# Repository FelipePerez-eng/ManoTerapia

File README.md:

# ManoTerapia

**METIE · Universidad de Ibagué · Ingeniería Electrónica**

**Equipo:** Felipe Perez · Brenda Guzman · David Solorzano

© 2026 Felipe Perez, Brenda Guzman y David Solorzano. Código y documentación originales bajo [licencia MIT](LICENSE). [Autoría, materiales de terceros y asistencia de IA](NOTICE.md).

Prototipo de mano robótica maestro–esclavo con ESP32, cinco potenciómetros y cinco servomotores MG90S. El dashboard permite usar control espejo, practicar gestos, ejecutar demostraciones, realizar rutinas y guardar resultados de pruebas en CSV.

## Qué archivo usar

| Necesitas… | Abre este archivo |
|---|---|
| Usar la interfaz | [dashboard/ManoTerapia.html](dashboard/ManoTerapia.html) |
| Cargar el programa al ESP32 | [firmware/ManoTerapia_ESP32/ManoTerapia_ESP32.ino](firmware/ManoTerapia_ESP32/ManoTerapia_ESP32.ino) |
| Abrir el proyecto electrónico | [hardware/kicad/Placa.kicad_pro](hardware/kicad/Placa.kicad_pro) |
| Consultar el esquema | [hardware/kicad/Placa.kicad_sch](hardware/kicad/Placa.kicad_sch) |
| Consultar la PCB | [hardware/kicad/Placa.kicad_pcb](hardware/kicad/Placa.kicad_pcb) |
| Ver pendientes y pruebas | [docs/estado.md](docs/estado.md) |
| Revisar los saltos esporádicos | [docs/estabilidad_electrica.md](docs/estabilidad_electrica.md) |

## Estructura

```text
ManoTerapia/
├── README.md
├── dashboard/
│   └── ManoTerapia.html
├── firmware/
│   └── ManoTerapia_ESP32/
│       └── ManoTerapia_ESP32.ino
├── hardware/
│   └── kicad/
│       ├── Placa.kicad_pro
│       ├── Placa.kicad_sch
│       ├── Placa.kicad_pcb
│       ├── fp-lib-table
│       ├── sym-lib-table
│       └── Library.pretty/
├── docs/
└── tests/
    └── verificar.cjs
```

Hay una sola copia vigente del dashboard y del firmware. Las versiones anteriores se consultan en el historial de Git, sin llenar la carpeta de archivos numerados. La organización no cambia el código operativo ni obliga a volver a cargarlo si ya estás usando la última versión.

## Puesta en marcha

1. Para programar la placa, abre el `.ino` en Arduino IDE desde su carpeta del mismo nombre. Selecciona tu placa ESP32 y puerto, e instala la biblioteca `ESP32Servo` si no está disponible.
2. Cierra el Monitor Serial antes de conectar el dashboard: utiliza una sola aplicación conectada al puerto a la vez.
3. Abre `dashboard/ManoTerapia.html` con Chrome o Edge de escritorio y pulsa **Conectar ESP32**. La comunicación usa **115200 baudios**. Si el navegador no admite Web Serial desde un archivo local, utiliza un contexto seguro compatible, como localhost.
4. Comprueba primero los porcentajes con los servos desactivados. Después activa el sistema y prueba movimientos lentos.
5. Para cambiar de sección durante una rutina o un gesto, primero pulsa **Finalizar**.

El HTML incorpora estilos, JavaScript y banner METIE; no necesita bibliotecas web externas. El historial de sesiones se guarda en el navegador. Exporta el CSV para conservar tus resultados. Cambiar de archivo, navegador u origen puede impedir acceder al historial anterior; exporta los datos antes de migrar.

## Funciones actuales

- **Control espejo:** la mano robótica sigue las lecturas de la mano maestra, con filtrado adaptativo, órdenes graduales e histéresis angular para reducir movimientos pequeños no deseados.
- **Activación:** antes de habilitar los servos, lee los cinco potenciómetros y calcula sus objetivos con la calibración vigente. Ya no impone siempre la posición abierta al activarlos. Esto no conoce la postura física previa ni garantiza eliminar el pico de corriente.
- **Rutinas:** activan los servos y esperan que el ESP32 confirme `SERVO ON` y modo `ROUTINE` antes de empezar. Si se apagan los servos o cambia el modo, la rutina queda en pausa y no valida ejercicios; **Reanudar rutina** vuelve a solicitar activación y conserva el paso. Muestran el objetivo y la lectura de cada dedo. La flexión intermedia admite de 30 % a 70 %; los demás pasos mantienen su margen de ±15 puntos. La posición se mantiene durante 1,2 segundos con recepción continua de datos.
- **Gestos:** mano abierta, puño, pulgar arriba, paz, señalamiento, pistolita y dedo medio. Una ventana flotante ofrece **Automático**, **Manual** y **Finalizar**, con opciones de minimizar y cerrar sin desplazar las tarjetas. Ocultar la ventana no finaliza una actividad.
- **Seguimiento:** sesiones locales, ciclos, muestras, actividades e informes CSV.

El corazón aparece como referencia deshabilitada: su reproducción requiere validar movimientos mecánicos que el control actual no implementa. Los sensores flex no se usan en el firmware vigente, aunque sus conectores aparecen en el diseño electrónico.

## Conexiones vigentes del firmware

| Dedo | GPIO del potenciómetro | GPIO del servo | RAW abierto | RAW cerrado |
|---|---:|---:|---:|---:|
| Pulgar | 33 | 23 | 4095 | 3800 |
| Índice | 32 | 22 | 4095 | 2700 |
| Medio | 35 | 21 | 4095 | 2500 |
| Anular | 34 | 19 | 4095 | 2800 |
| Meñique | 36 | 18 | 4095 | 3100 |

Estas correspondencias conservan las correcciones del usuario. No equivalen necesariamente al orden numérico de los conectores en la placa.

- Pulsador: **GPIO 4 a GND**, con `INPUT_PULLUP` y antirrebote de 60 ms.
- LED: **GPIO 13**, con resistencia de 330 Ω hacia el LED y GND.
- Potenciómetros: alimentación de **3,3 V**.
- Servos: **MG90S**, fuente externa de **5 V** indicada por el usuario. Capacidad en amperios pendiente de confirmar.
- Mantener una referencia GND común entre señales del ESP32 y alimentación de los servos.

La lectura disminuye al cerrar la mano. La calibración utiliza esos extremos sin invertir las señales de los servos. Un RAW que permanezca fijo en 4095 al mover el potenciómetro requiere revisar la lectura y sus conexiones; cambiar la calibración no repara una conexión intermitente.

## KiCad

Esquemático compartido por el equipo. Los conectores flex aparecen en el diseño, pero no se utilizan en el firmware vigente. Para consultar la edición actual, abre el archivo `.kicad_sch` del proyecto.

Los archivos proceden del proyecto `Placa` de METIE, creado con **KiCad 10**. Abre `Placa.kicad_pro` para trabajar con esquema y PCB. Se incluyen el símbolo ESP32 y sus huellas locales. En esta copia se normalizó la tabla de huellas para evitar entradas duplicadas y se añadió una tabla de símbolos con ruta relativa.

El esquema y la PCB no se rediseñaron durante la organización. Los modelos 3D externos no se incluyen; las huellas pueden conservar referencias a `KICAD_USER_3DMODEL_DIR`. No publicar archivos de fabricación como validados hasta revisar el diseño y su correspondencia con el montaje.

## Estado y límites

El usuario reportó mejoras tras resoldar conexiones y probar las variantes de calibración y filtrado. **Siguen pendientes los pequeños saltos esporádicos de los servos y la respuesta intermitente del pulsador.** No se consideran resueltos por la reorganización.

El dashboard mide señales de los potenciómetros de la mano maestra. No mide la posición física de la mano esclava. Una demostración terminada indica que acabó la secuencia de órdenes, no que la postura física se haya verificado. Las rutinas son demostraciones del prototipo académico, no un protocolo clínico validado.

## Cómo citar el proyecto

Si utilizas ManoTerapia como referencia en una presentación, trabajo académico o investigación, por favor incluye esta cita:

> Perez, F., Guzman, B., y Solorzano, D. (2026). *ManoTerapia* [Software de prototipo académico]. GitHub. https://github.com/FelipePerez-eng/ManoTerapia

El archivo [CITATION.cff](CITATION.cff) facilita la opción **Cite this repository** de GitHub. La cita académica se solicita como reconocimiento; la condición de MIT es conservar el aviso de copyright y la licencia en las copias o partes sustanciales correspondientes.

## Desarrollo con asistencia de IA

El proyecto contó con asistencia de **ChatGPT/Codex de OpenAI** para apoyar la programación, el diseño de la interfaz, la documentación, la revisión de código y las pruebas simuladas. La revisión e integración física corresponden al equipo. Esta asistencia no implica certificación técnica ni validación clínica.

Consulta [NOTICE.md](NOTICE.md) para el alcance de la licencia y los materiales de terceros, incluidos los recursos institucionales y las bibliotecas externas.

## Pruebas y versiones

Con Node.js, desde la carpeta principal:

```sh
node tests/verificar.cjs
```

Las pruebas son simuladas y no sustituyen compilar el firmware en Arduino IDE ni probar el prototipo. Consultar [docs/estado.md](docs/estado.md) para distinguir las verificaciones realizadas de las pendientes.

Repositorio: [FelipePerez-eng/ManoTerapia](https://github.com/FelipePerez-eng/ManoTerapia). Cada cambio debe quedar descrito en un commit; las versiones antiguas se recuperan desde ese historial. No subir datos personales de participantes, CSV de sesiones ni credenciales.

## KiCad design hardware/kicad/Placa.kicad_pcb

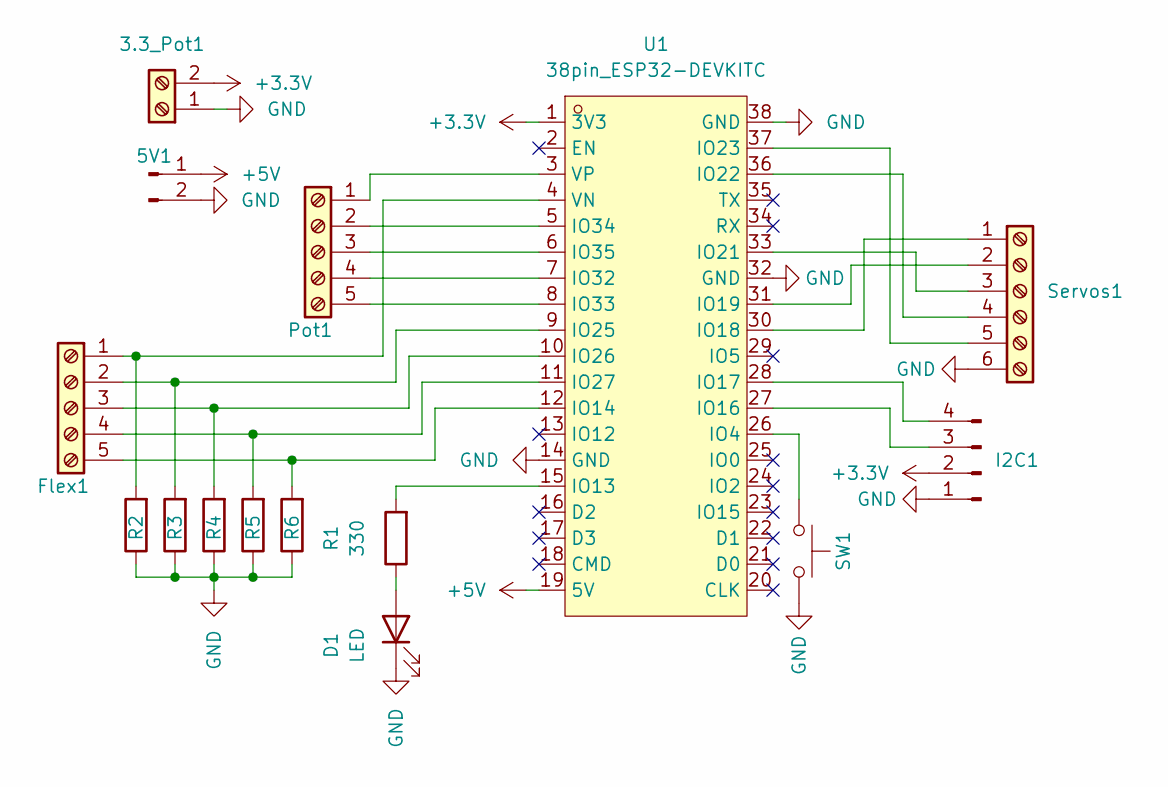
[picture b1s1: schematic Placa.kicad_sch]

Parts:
3.3_Pot1: Screw_Terminal_01x02; TerminalBlock_MaiXu_MX126-5.0-02P_1x02_P5.00mm
5V1: Conn_01x02_Pin; PinSocket_1x02_P2.54mm_Vertical
D1: LED; LED_D3.0mm
Flex1: Screw_Terminal_01x05; TerminalBlock_MaiXu_MX126-5.0-05P_1x05_P5.00mm
I2C1: Conn_01x04_Pin; PinHeader_1x04_P2.54mm_Vertical
Pot1: Screw_Terminal_01x05; TerminalBlock_MaiXu_MX126-5.0-05P_1x05_P5.00mm
R1, R2, R3, R4, R5, R6: 330; R_Axial_DIN0207_L6.3mm_D2.5mm_P10.16mm_Horizontal
SW1: SW_Push; SW_PUSH_6mm
Servos1: Screw_Terminal_01x06; TerminalBlock_MaiXu_MX126-5.0-06P_1x06_P5.00mm
U1: 38pin_ESP32-DEVKITC; Z_ESP32_DevKitC_38pin_socket; MPN ESP32-DevKitC; LCSC Part C571180

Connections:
+3.3V: 3.3_Pot1.2, I2C1.2, U1.1 (3V3)
+5V: 5V1.1, U1.19 (5V)
GND: 3.3_Pot1.1, 5V1.2, D1.1 (K), I2C1.1, R2.1, R3.1, R4.1, R5.1, R6.1, SW1.2, Servos1.6, U1.14 (GND), U1.32 (GND), U1.38 (GND)
unnamed: D1.2 (A), R1.1
unnamed: Flex1.1, R2.2, U1.4 (VN)
unnamed: Flex1.2, R3.2, U1.9 (IO25)
unnamed: Flex1.3, R4.2, U1.10 (IO26)
unnamed: Flex1.4, R5.2, U1.11 (IO27)
unnamed: Flex1.5, R6.2, U1.12 (IO14)
unnamed: I2C1.3, U1.27 (IO16)
unnamed: I2C1.4, U1.28 (IO17)
unnamed: Pot1.1, U1.3 (VP)
unnamed: Pot1.2, U1.5 (IO34)
unnamed: Pot1.3, U1.6 (IO35)
unnamed: Pot1.4, U1.7 (IO32)
unnamed: Pot1.5, U1.8 (IO33)
unnamed: Servos1.1, U1.30 (IO18)
unnamed: Servos1.2, U1.31 (IO19)
unnamed: Servos1.3, U1.33 (IO21)
unnamed: Servos1.4, U1.36 (IO22)
unnamed: Servos1.5, U1.37 (IO23)
unnamed: SW1.1, U1.26 (IO4)
unnamed: R1.2, U1.15 (IO13)

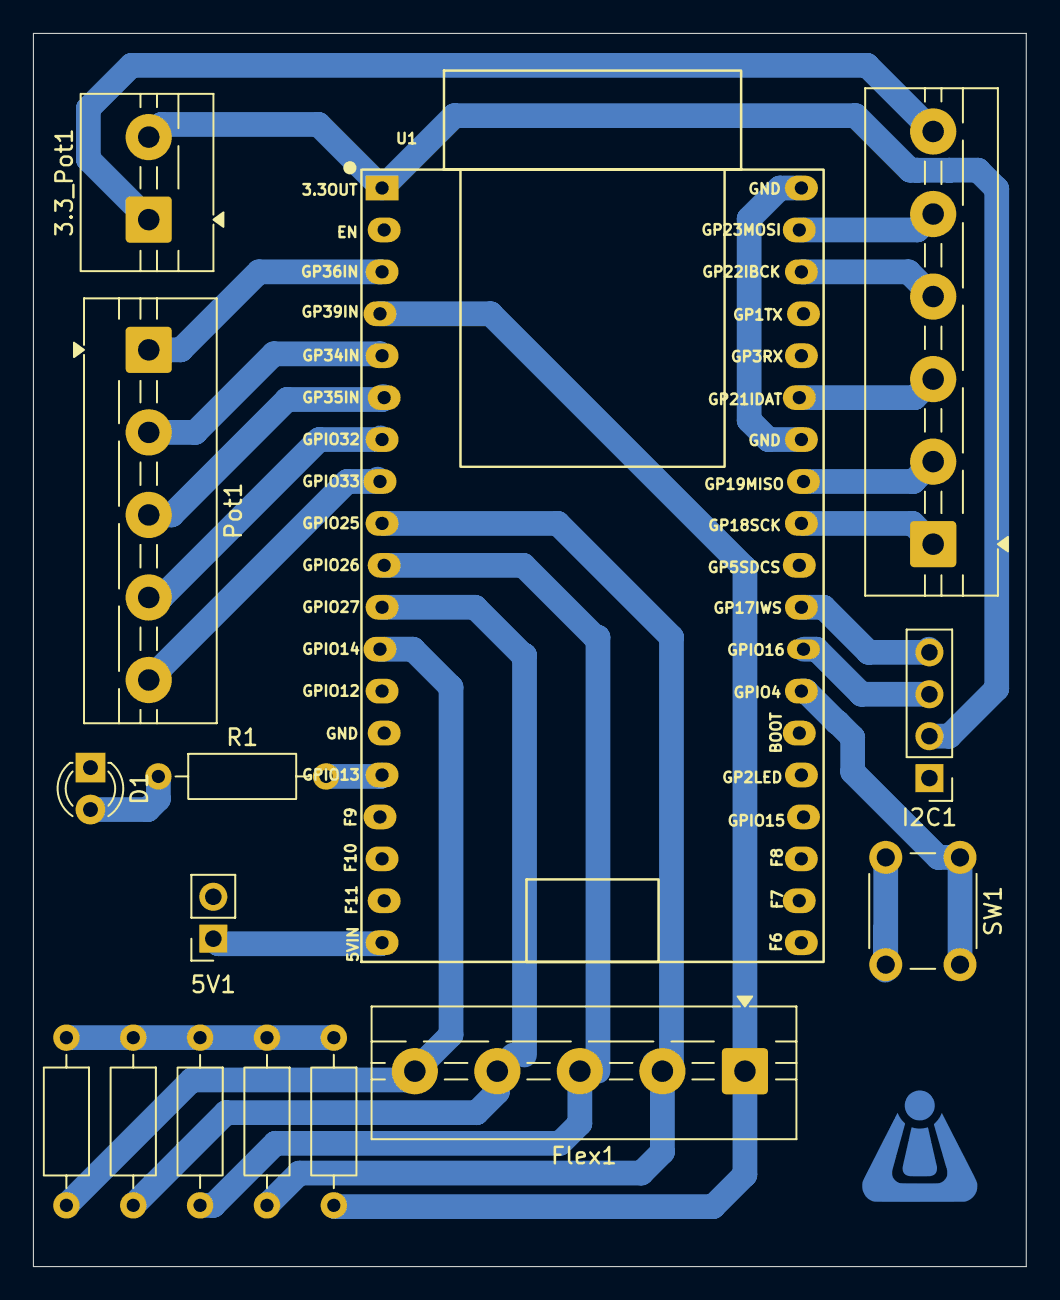
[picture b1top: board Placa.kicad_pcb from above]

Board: 2 copper layers, 60.1 x 74.7 mm, 16 parts (1 on the bottom side), 23 nets.

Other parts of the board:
-: LOGO
